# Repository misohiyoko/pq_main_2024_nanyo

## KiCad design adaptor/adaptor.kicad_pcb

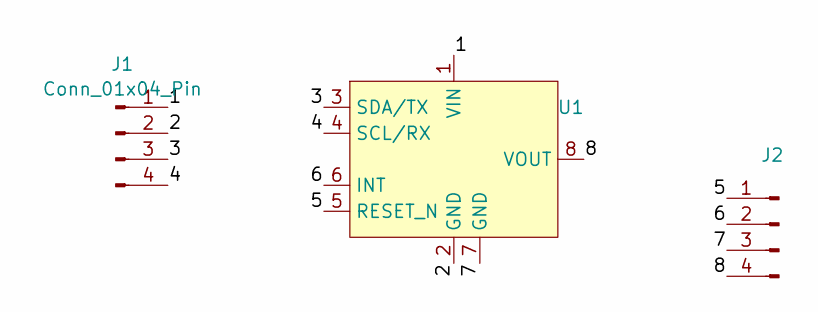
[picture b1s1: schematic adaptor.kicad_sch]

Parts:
J1, J2: Conn_01x04_Pin; PinHeader_1x04_P2.54mm_Vertical
U1: AE-BNO055

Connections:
/1: J1.1, U1.1 (VIN)
/2: J1.2, U1.2 (GND)
/3: J1.3, U1.3 (SDA/TX)
/4: J1.4, U1.4 (SCL/RX)
/5: J2.1, U1.5 (RESET_N)
/6: J2.2, U1.6 (INT)
/7: J2.3, U1.7 (GND)
/8: J2.4, U1.8 (VOUT)

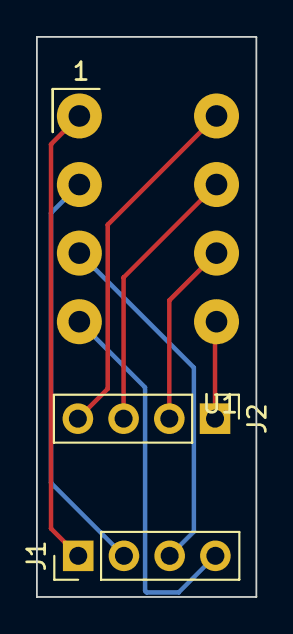
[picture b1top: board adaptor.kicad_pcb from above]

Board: 2 copper layers, 12.2 x 31.1 mm, 3 parts (0 on the bottom side), 8 nets.

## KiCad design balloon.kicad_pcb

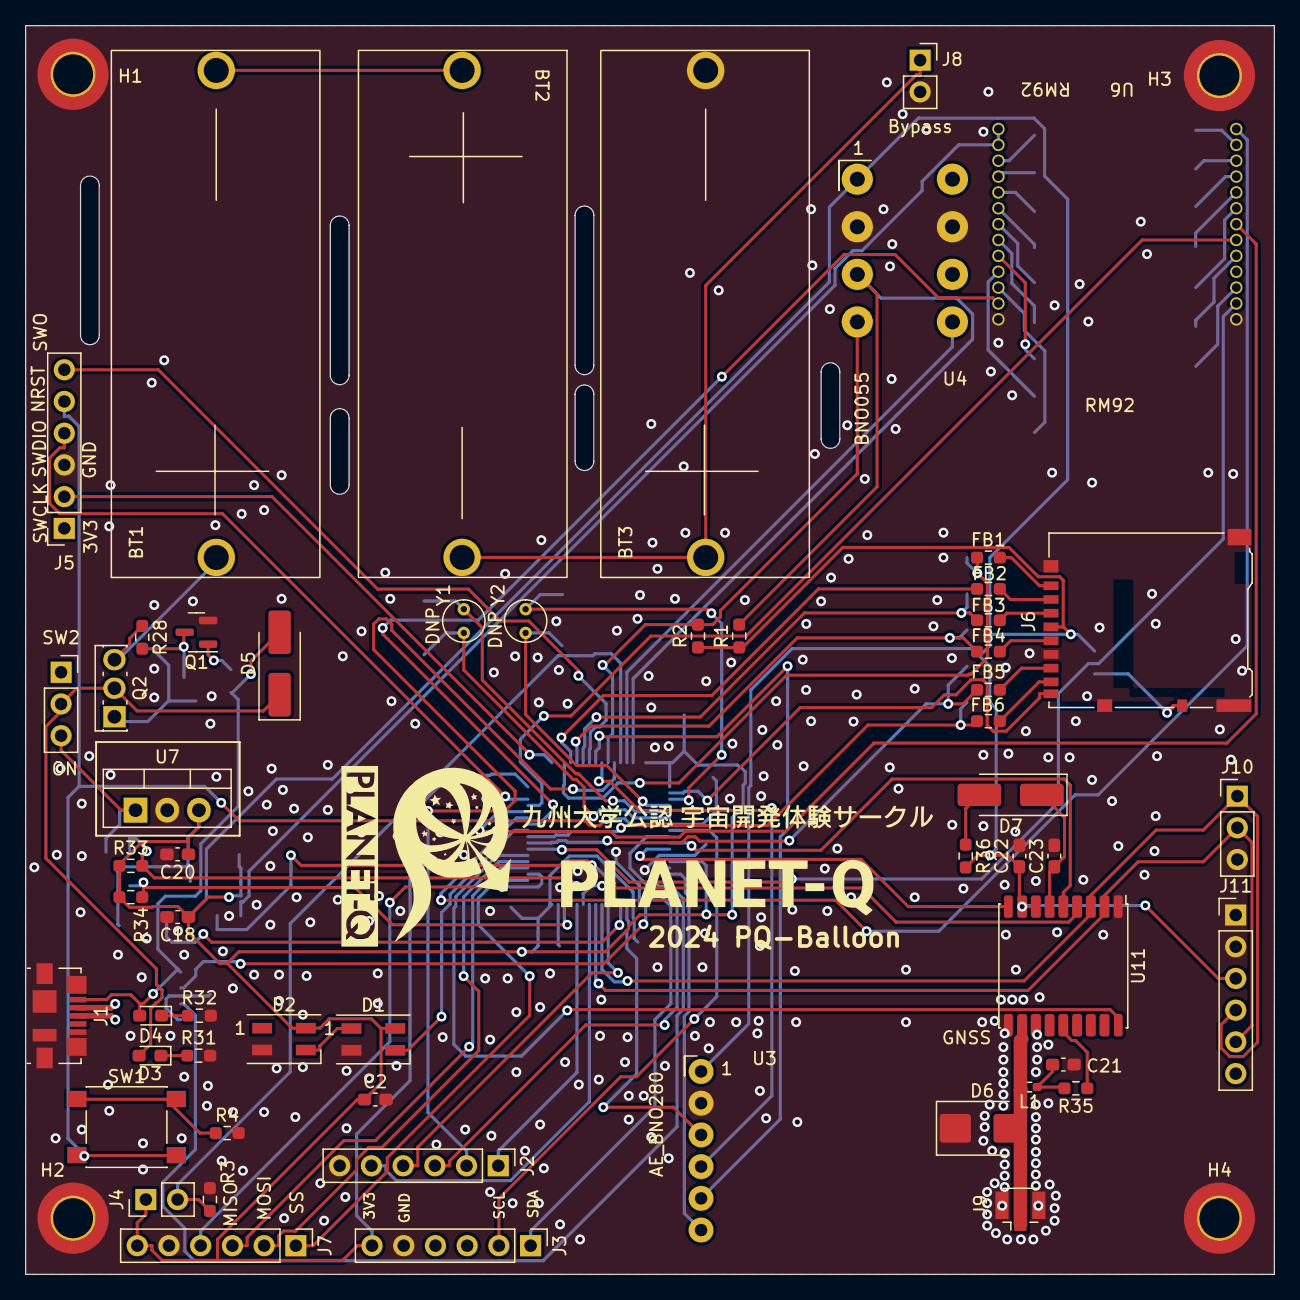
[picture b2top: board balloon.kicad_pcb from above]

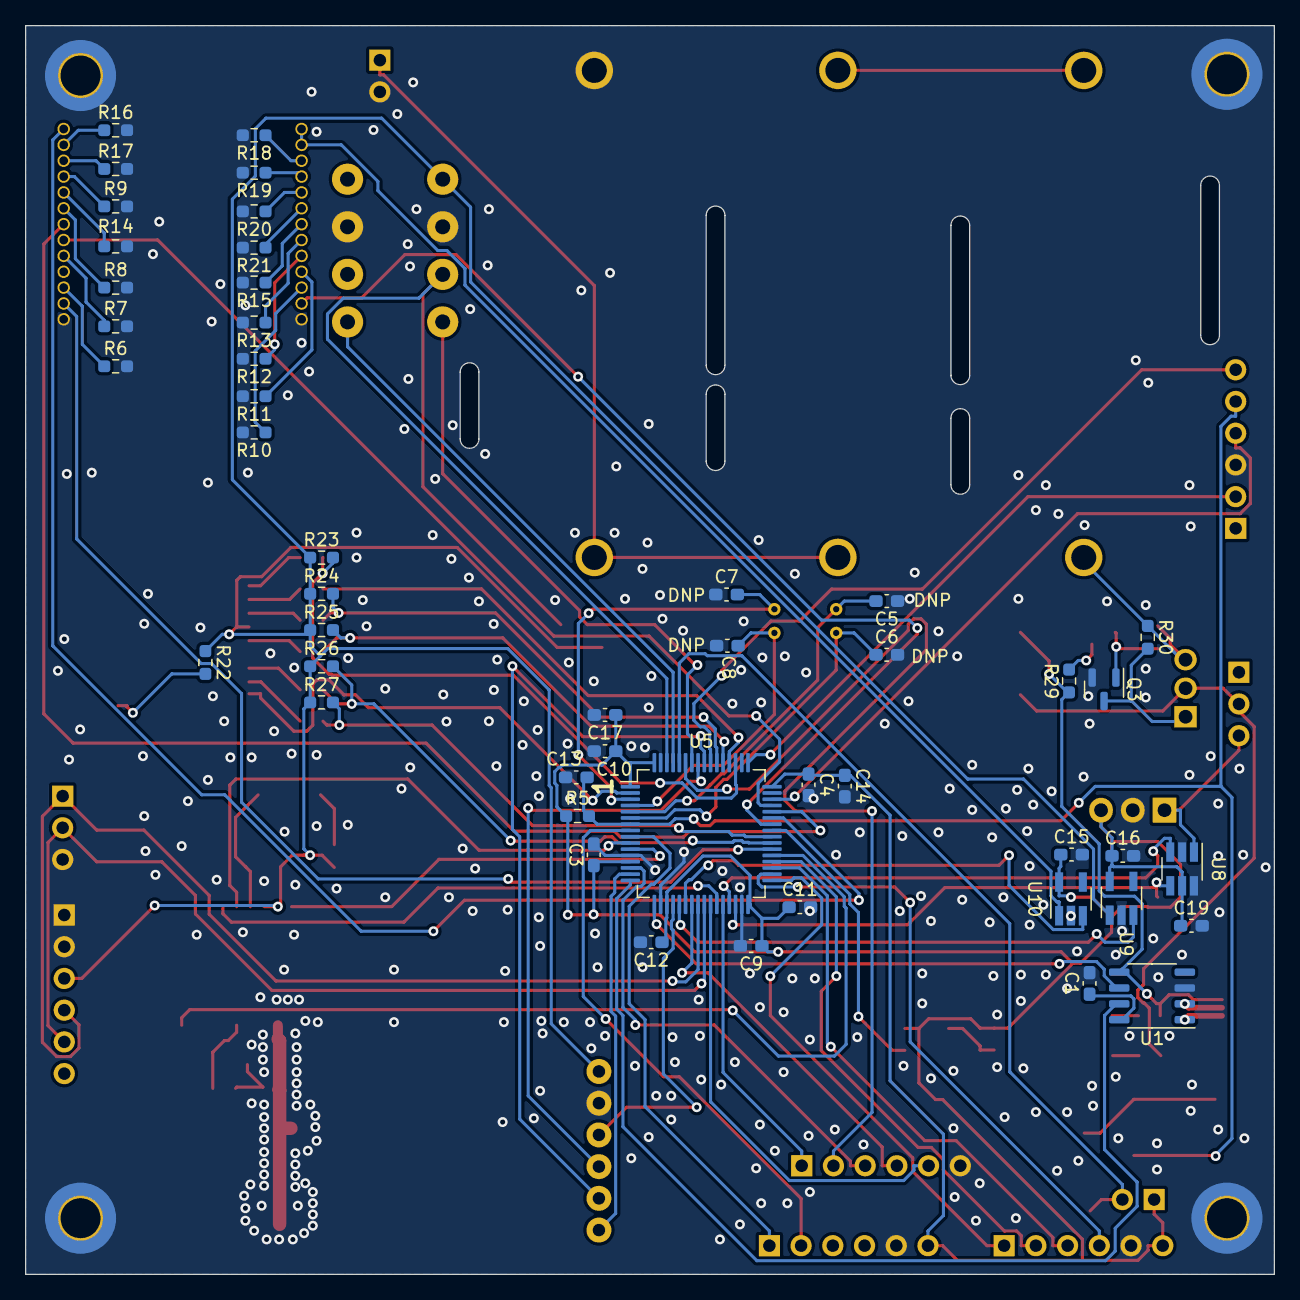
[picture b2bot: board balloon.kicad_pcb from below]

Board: 2 copper layers, 100.0 x 100.0 mm, 108 parts (48 on the bottom side), 100 nets.

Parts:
BT1, BT2, BT3: CR123A
C1, C2, C3, C4, C9, C10, C11, C12, C13, C15, C16, C19, C21, C22, C23: 100n; C_0603_1608Metric_Pad1.08x0.95mm_HandSolder
C5, C6, C7, C8: C; C_0603_1608Metric_Pad1.08x0.95mm_HandSolder
C14, C17, C18, C20: 4.7u; C_0603_1608Metric_Pad1.08x0.95mm_HandSolder
D1, D2: SK6812MINI; LED_SK6812MINI_PLCC4_3.5x3.5mm_P1.75mm
D3, D4: OSG50603C1E; LED_0603_1608Metric_Pad1.05x0.95mm_HandSolder
D5: RS1M; D_SMA_Handsoldering
D6: SMBJ45CA; D_SMB
D7: D; D_SMA_Handsoldering
FB1, FB2, FB3, FB4, FB5, FB6: BLM18R; R_0603_1608Metric_Pad0.98x0.95mm_HandSolder
H1, H2, H3, H4: MountingHole; MountingHole_3.2mm_M3_ISO7380_Pad_TopBottom
J1: USB_B_Micro; USB_Micro-B_Molex_47346-0001
J2, J3, J7, J11: Conn_01x06_Socket; PinHeader_1x06_P2.54mm_Vertical
J4: Conn_01x02_Socket; PinHeader_1x02_P2.54mm_Vertical
J5: Writing Connector; PinSocket_1x06_P2.54mm_Vertical
J6: Micro_SD_Card_Det_Hirose_DM3AT; microSD_HC_Hirose_DM3AT-SF-PEJM5
J8: Bypass; PinSocket_1x02_P2.54mm_Vertical
J9: Conn_Coaxial; U.FL_Hirose_U.FL-R-SMT-1_Vertical
J10: Conn_01x03_Socket; PinHeader_1x03_P2.54mm_Vertical
L1: BLM18PG471SN1D; R_0402_1005Metric_Pad0.72x0.64mm_HandSolder
Q1, Q3: BSS138; SOT-23
Q2: 2SJ681; SIPAK_Vertical
R1, R2, R4, R31, R32, R33, R34: 2.2k; R_0603_1608Metric_Pad0.98x0.95mm_HandSolder
R3, R5, R22, R28: 10k; R_0603_1608Metric_Pad0.98x0.95mm_HandSolder
R6, R7, R8, R9, R10, R11, R12, R13, R14, R15, R16, R17, R18, R19, R20, R21, R30: 47k; R_0603_1608Metric_Pad0.98x0.95mm_HandSolder
R23, R24, R25, R26, R27: 22k; R_0603_1608Metric_Pad0.98x0.95mm_HandSolder
R29, R35: 100; R_0603_1608Metric_Pad0.98x0.95mm_HandSolder
R36: 1k; R_0603_1608Metric_Pad0.98x0.95mm_HandSolder
SW1: DTS-63-F-N-V-RED; SW_SPST_PTS645
SW2: SW_SPDT; PinSocket_1x03_P2.54mm_Vertical
U1: CH340N; SOP-8_3.9x4.9mm_P1.27mm
U3: AE_BME280; AE_BNE280
U4: AE_BNO055; AE-BNO055
U5: STM32L431RBTx; LQFP-64_10x10mm_P0.5mm
U6: RM92A
U7: M78AR033-1; TO-220-3_Vertical
U8: MCP3425A0T-ECH; SOT-23-6_Handsoldering
U9, U10: TCK107AF; SOT-23-5_HandSoldering
U11: MAX-M10S; ublox_MAX
Y1, Y2: Crystal; Crystal_C38-LF_D3.0mm_L8.0mm_Vertical

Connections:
+3V3: C2.1, C3.1, C4.1, C9.1, C10.1, C11.1, C12.1, C14.1, C15.1, C16.1, C17.1, C18.1, C19.1, C20.1, D1.4 (VDD), D2.4 (VDD), J3.6, J4.1, J7.6, R5.1, R33.1, R34.1, U5.1 (VBAT), U5.13 (VDDA), U5.19 (VDD), U5.32 (VDD), U5.48 (VDD), U5.64 (VDD), U7.3 (VO), U8.5 (Vdd), U9.5 (VIN), U10.5 (VIN)
/BNO055_RESET: U4.5 (RESET_N), U5.61 (PB8)
/BOOT0: J4.2, R3.1, U5.60 (PH3)
/CTRL_COMM: U5.22 (PA6), U10.3 (CTRL)
/CTRL_SENSE: U5.21 (PA5), U9.3 (CTRL)
/GPS_INT: U5.10 (PC2), U11.5 (EXTINT)
/GPS_RESET: U5.11 (PC3), U11.9 (~RESET)
/GPS_SAFE: U5.37 (PC6), U11.18 (~SAFEBOOT)
/I2C1_SCL: R2.2, U4.4 (SCL/RX), U5.58 (PB6)
/I2C1_SDA: R1.2, U4.3 (SDA/TX), U5.62 (PB9)
/I2C2_SCL: R33.2, U5.29 (PB10), U8.3 (SCL)
/I2C2_SDA: R34.2, U5.30 (PB11), U8.4 (SDA)
/I2C3_SCL: J3.2, U5.8 (PC0)
/I2C3_SDA: J3.1, U5.9 (PC1)
/LED_OUT: D1.3 (DIN), U5.41 (PA8)
/LPTIM1_IN: U5.27 (PB1), U11.4 (TIMEPULSE)
/MAX-M10S/VBKUP: C23.1, D7.1 (K), U11.6 (V_BCKP)
/MAX-M10S/VIN: C22.1, J6.4 (VDD), J11.3, R1.1, R2.1, R22.1, R23.1, R24.1, R25.1, R26.1, R27.1, R36.2, U3.1 (VDD), U4.1 (VIN), U9.1 (VOUT), U11.7 (VCC_IO), U11.8 (VCC)
/NRST: C13.1, J5.5, R5.2, SW1.2, U5.7 (NRST)
/OSC32_IN: C7.2, U5.3 (PC14), Y2.2
/OSC32_OUT: C8.1, U5.4 (PC15), Y2.1
/OSC_IN: C5.2, U5.5 (PH0), Y1.2
/OSC_OUT: C6.1, U5.6 (PH1), Y1.1
/PA0: J2.3, U5.14 (PA0)
/PA7: J2.4, U5.23 (PA7)
/PB0: J2.5, U5.26 (PB0)
/PB2: J2.1, U5.28 (PB2)
/PB7: J2.2, U5.59 (PB7)
/PowerSource/5VIN: D4.2 (A), D5.2 (A), J1.1 (VBUS), R29.1, U1.5 (VCC)
/PowerSource/VCOMM: U6.14 (VDDRF), U6.15 (VCC), U10.1 (VOUT)
/PowerSource/VIN: SW2.3 (C), U7.1 (VI), U8.1 (Vin+)
/RM92A_RESET: U5.38 (PC7), U6.2 (RESET_N)
/SDMMC_CLK: FB4.1, R25.2, U5.53 (PC12)
/SDMMC_CMD: FB3.1, R24.2, U5.54 (PD2)
/SDMMC_D0: FB5.1, R26.2, U5.39 (PC8)
/SDMMC_D1: FB6.1, R27.2, U5.40 (PC9)
/SDMMC_D2: FB1.1, R23.2, U5.51 (PC10)
/SDMMC_D3: FB2.1, U5.52 (PC11)
/SD_DET: J6.9 (DET_B), U5.2 (PC13)
/SPI1_CLK: U3.6 (SCK/SCL), U5.15 (PA1)
/SPI1_MISO: U3.5 (MISO/GND), U5.56 (PB4)
/SPI1_MOSI: U3.4 (MOSI/SDA), U5.57 (PB5)
/SPI1_SS: U3.3 (CSB/VDD), U5.20 (PA4)
/SPI2_MISO: J7.3, U5.35 (PB14)
/SPI2_MOSI: J7.2, U5.36 (PB15)
/SPI2_NSS: J7.1, U5.33 (PB12)
/SPI2_SCK: J7.4, U5.34 (PB13)
/SWCLK: J5.2, U5.49 (PA14)
/SWDIO: J5.4, U5.46 (PA13)
/SWO: J5.6, U5.55 (PB3)
/USART1_CTS: U5.44 (PA11), U6.7 (RTS)
/USART1_RTS: U5.45 (PA12), U6.6 (CTS)
/USART1_RX: U5.43 (PA10), U6.13 (TX)
/USART1_TX: U5.42 (PA9), U6.25 (RX)
/USART2_RX: U1.6 (TXD), U5.17 (PA3)
/USART2_TX: U1.7 (RXD), U5.16 (PA2)
/USART3_RX: J10.2, J11.5, U5.25 (PC5), U11.2 (TXD)
/USART3_TX: J10.1, J11.4, U5.24 (PC4), U11.3 (RXD)
/USBD+: J1.3 (D+), U1.1 (UD+)
/USBD-: J1.2 (D-), U1.2 (UD-)
GND1: BT3.2 (-), C1.2, C2.2, C3.2, C4.2, C5.1, C6.2, C7.1, C8.2, C9.2, C10.2, C11.2, C12.2, C13.2, C14.2, C15.2, C16.2, C17.2, C18.2, C19.2, C20.2, C21.2, C22.2, C23.2, D1.2 (VSS), D2.2 (VSS), D6.1 (A1), H1.1, H2.1, H3.1, H4.1, J1.5 (GND), J1.6 (Shield), J2.6, J3.5, J5.3, J6.6 (VSS), J6.11 (SHIELD), J7.5, J8.2, J9.2 (Ext), J10.3, J11.1, J11.2, Q1.2 (S), Q3.2 (S), R3.2, R4.2, R6.2, R7.2, R8.2, R9.2, R10.2, R11.2, R12.2, R13.2, R14.1, R15.2, R16.2, R17.2, R18.2, R19.2, R20.2, R21.2, R31.2, R32.2, U1.3 (GND), U3.2 (GND), U4.2 (GND), U4.7 (GND), U5.12 (VSSA), U5.18 (VSS), U5.31 (VSS), U5.47 (VSS), U5.63 (VSS), U6.1 (GND), U6.26 (GND), U7.2 (GND), U8.2 (Vss), U8.6 (Vin-), U9.2 (GND), U10.2 (GND), U11.1 (GND), U11.10 (GND), U11.12 (GND)
unnamed: BT1.1 (+), Q2.3 (S), R28.1, R30.1
unnamed: BT1.2 (-), BT2.1 (+)
unnamed: BT2.2 (-), BT3.1 (+), J8.1
unnamed: C21.1, L1.1, R35.2
unnamed: D1.1 (DOUT), D2.3 (DIN)
unnamed: D3.2 (A), D5.1 (K), Q2.2 (D), SW2.2 (B)
unnamed: D3.1 (K), R31.1
unnamed: D4.1 (K), R32.1
unnamed: D6.2 (A2), J9.1 (In), L1.2, U11.11 (RF_IN)
unnamed: D7.2 (A), R36.1
unnamed: FB4.2, J6.5 (CLK)
unnamed: FB3.2, J6.3 (CMD)
unnamed: FB5.2, J6.7 (DAT0)
unnamed: FB6.2, J6.8 (DAT1)
unnamed: FB1.2, J6.1 (DAT2)
unnamed: FB2.2, J6.2 (DAT3/CD)
unnamed: J6.10 (DET_A), R22.2
unnamed: Q1.3 (D), Q3.1 (G), R28.2
unnamed: Q1.1 (G), R29.2
unnamed: Q2.1 (G), Q3.3 (D), R30.2
unnamed: R4.1, SW1.1
unnamed: C1.1, U1.8 (V3)
unnamed: R14.2, U6.9 (BOOT0)
unnamed: R15.1, U6.20 (JNTRST)
unnamed: R10.1, U6.24 (JTCK/SWCLK)
unnamed: R12.1, U6.22 (JTDI)
unnamed: R13.1, U6.21 (JTDO)
unnamed: R11.1, U6.23 (JTMS/SWDIO)
unnamed: R8.1, U6.8 (PA8)
unnamed: R9.1, U6.10 (PB2)
unnamed: R7.1, U6.5 (PB7)
unnamed: R6.1, U6.3 (PC13)
unnamed: R17.1, U6.11 (SCL)
unnamed: R16.1, U6.12 (SDA)
unnamed: R20.1, U6.18 (SPI_MISO)
unnamed: R21.1, U6.19 (SPI_MOSI)
unnamed: R19.1, U6.17 (SPI_SCK)
unnamed: R18.1, U6.16 (SPI_SS)
unnamed: R35.1, U11.14 (VCC_RF)

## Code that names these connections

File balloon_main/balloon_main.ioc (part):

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Mcu.Name=STM32L431R(B-C)Tx
Mcu.Package=LQFP64
Mcu.UserName=STM32L431RBTx
PA1.GPIOParameters=GPIO_PuPd
PA1.GPIO_PuPd=GPIO_PULLUP
PA1.Mode=Full_Duplex_Master
PA1.Signal=SPI1_SCK
PA10.Mode=Asynchronous
PA10.Signal=USART1_RX
PA11.Signal=USART1_CTS
PA12.Signal=USART1_RTS
PA13\ (JTMS-SWDIO).Mode=Trace_Asynchronous_SW
PA13\ (JTMS-SWDIO).Signal=SYS_JTMS-SWDIO
PA14\ (JTCK-SWCLK).Mode=Trace_Asynchronous_SW
PA14\ (JTCK-SWCLK).Signal=SYS_JTCK-SWCLK
PA2.Mode=Asynchronous
PA2.Signal=USART2_TX
PA3.Mode=Asynchronous
PA3.Signal=USART2_RX
PA4.GPIOParameters=GPIO_Label
PA4.GPIO_Label=SPI1_Cs
PA4.Signal=GPIO_Output
PA5.GPIOParameters=GPIO_Label
PA5.GPIO_Label=CTRL_SENSE
PA5.Signal=GPIO_Output
PA6.GPIOParameters=GPIO_Label
PA6.GPIO_Label=CTRL_COMM
PA6.Signal=GPIO_Output
PA8.GPIOParameters=GPIO_Speed
PA8.GPIO_Speed=GPIO_SPEED_FREQ_HIGH
PA8.Signal=S_TIM1_CH1
PA9.Mode=Asynchronous
PA9.Signal=USART1_TX
PB1.Mode=Counts_external_clock_standalone_1X_occur1
PB1.Signal=LPTIM2_IN1
PB10.Mode=I2C
PB10.Signal=I2C2_SCL
PB11.Mode=I2C
PB11.Signal=I2C2_SDA
PB12.Mode=NSS_Signal_Hard_Output
PB12.Signal=SPI2_NSS
PB13.Mode=Full_Duplex_Master
PB13.Signal=SPI2_SCK
PB14.Mode=Full_Duplex_Master
PB14.Signal=SPI2_MISO
PB15.Mode=Full_Duplex_Master
PB15.Signal=SPI2_MOSI
PB3\ (JTDO-TRACESWO).Mode=Trace_Asynchronous_SW
PB3\ (JTDO-TRACESWO).Signal=SYS_JTDO-SWO
PB4\ (NJTRST).GPIOParameters=GPIO_PuPd
PB4\ (NJTRST).GPIO_PuPd=GPIO_PULLUP
PB4\ (NJTRST).Mode=Full_Duplex_Master
PB4\ (NJTRST).Signal=SPI1_MISO
PB5.GPIOParameters=GPIO_PuPd
PB5.GPIO_PuPd=GPIO_PULLUP
PB5.Mode=Full_Duplex_Master
PB5.Signal=SPI1_MOSI
PB6.Mode=I2C
PB6.Signal=I2C1_SCL
PB8.GPIOParameters=GPIO_Label
PB8.GPIO_Label=BNO055_RESET
PB8.Signal=GPIO_Output
PB9.Mode=I2C
PB9.Signal=I2C1_SDA
PC0.Mode=I2C
PC0.Signal=I2C3_SCL
PC1.Mode=I2C
PC1.Signal=I2C3_SDA
PC10.Signal=SDMMC1_D2
PC11.Signal=SDMMC1_D3
PC12.Mode=SD_1_bit
PC12.Signal=SDMMC1_CK
PC13.GPIOParameters=GPIO_Label
PC13.GPIO_Label=SD_DET
PC13.Signal=GPIO_Input
PC14-OSC32_IN\ (PC14).Signal=RCC_OSC32_IN
PC15-OSC32_OUT\ (PC15).Signal=RCC_OSC32_OUT
PC2.GPIOParameters=GPIO_Label
PC2.GPIO_Label=GPS_INT
PC2.Signal=GPIO_Input
PC3.GPIOParameters=GPIO_Label
PC3.GPIO_Label=GPS_RESET
PC3.Signal=GPIO_Output
PC4.Mode=Asynchronous
PC4.Signal=USART3_TX
PC5.Mode=Asynchronous
PC5.Signal=USART3_RX
PC6.GPIOParameters=GPIO_Label
PC6.GPIO_Label=GPS_SAFE
PC6.Signal=GPIO_Analog
PC7.GPIOParameters=GPIO_Label
PC7.GPIO_Label=RM92A_RESET
PC7.Signal=GPIO_Output
PC8.Mode=SD_1_bit
PC8.Signal=SDMMC1_D0
PC9.Signal=SDMMC1_D1
PD2.Mode=SD_1_bit
PD2.Signal=SDMMC1_CMD
RCC.HSE_VALUE=8000000
RCC.SYSCLKFreq_VALUE=80000000
RCC.SYSCLKSource=RCC_SYSCLKSOURCE_PLLCLK
board=custom

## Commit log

2024-04-13 add stm32 project
2024-04-14 make board
2024-04-14 add saved
2024-04-16 replace PCB
2024-04-17 add stmcube
2024-04-18 change gnss
2024-04-18 add icon
2024-04-19 code
2024-04-19 change conn
2024-04-19 add rtos
2024-04-20 set gerber
2024-04-21 add uart
2024-04-22 add lib
2024-04-23 change schematics
2024-04-23 change pcb
2024-05-27 code update
2024-05-27 add Task
2024-05-29 add proto
2024-05-31 add gitignore
2024-05-31 change pow
2024-07-07 add communication
